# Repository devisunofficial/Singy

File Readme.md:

# Singy

This is an mp3 player I build because I wanted a mp3 player because having an MP3 player seems cool but not wanted to buy one.
It is inspired from iPod but it is not that good(I never had iPod). I just find Screen and Circular Controller a nice design.

### Features:

 - Minimilist. Just a display and Trackpad
 - 2.8 inch non touch display
 - Circular trackpad (but no haptics) {for me adding haptics is too much}
 - Have Wifi, Bluetooth and 3.5mm Headphone Jack (but I will only use 3.5mm Jack)
 - Inbuilt DAC and AMP (I hope it has good sound quality)

### CAD Model:
Everything fits together using Glue.

It has 3 separate printed pieces. The BackPanel, the shell , and Front Panel to cover electronics.

Made in Autodesk Fusion.
I didn't inserted 3D model for Display and Trackpad (Because I can't find)
So I will add this when it is completed!!

### PCB:
Here's my PCB! It was made in KiCad. 

Schematic : 
PCB Footprint : 

### Firmware Overview:
Currently Firmware is underdevelopment so there is some time to finished product.
This MP3 player uses CPP for firmware.
Features after completion:
 - Three ways to add new songs
    1. Directly in SD-Card
    2. Through USB Port
    3. Over Wi-fi.
 - The most important feature is it is offline but the Library is always updated
 - In final version, you need to save some of your favourite songs, and at your preferred date and time library will be updated.(Might need a server or device that has wifi and can run continously for this) 

 I might add more in the future! That's the only plan I have now

### BOM Table:
|S. No.|Name|Use|Quantity|
|------|----|---|-----------|
|1|PCB|Main Circuit|1|
|2|ESP32-S3 Wroom 1|Microcontroller|1|
|3|2.8inch Display|Display|1|
|4|Cirque TrackPad|Controlling and Navigation|1|
|5|Battery|Power Source |1|

### Assembly Instructions:
1. Flash PCB with Firmware, connect everything and check if everything is working or not
2. If Everything works, stick battery and PCB to their Respective places.
3. Also Stick Display and TrackPad Carefully to their places
4. Sltick all bodies together and Voila you have an MP3 player

### Extra Stuff:
 Not anything for now but I will surely have when the build is complete.

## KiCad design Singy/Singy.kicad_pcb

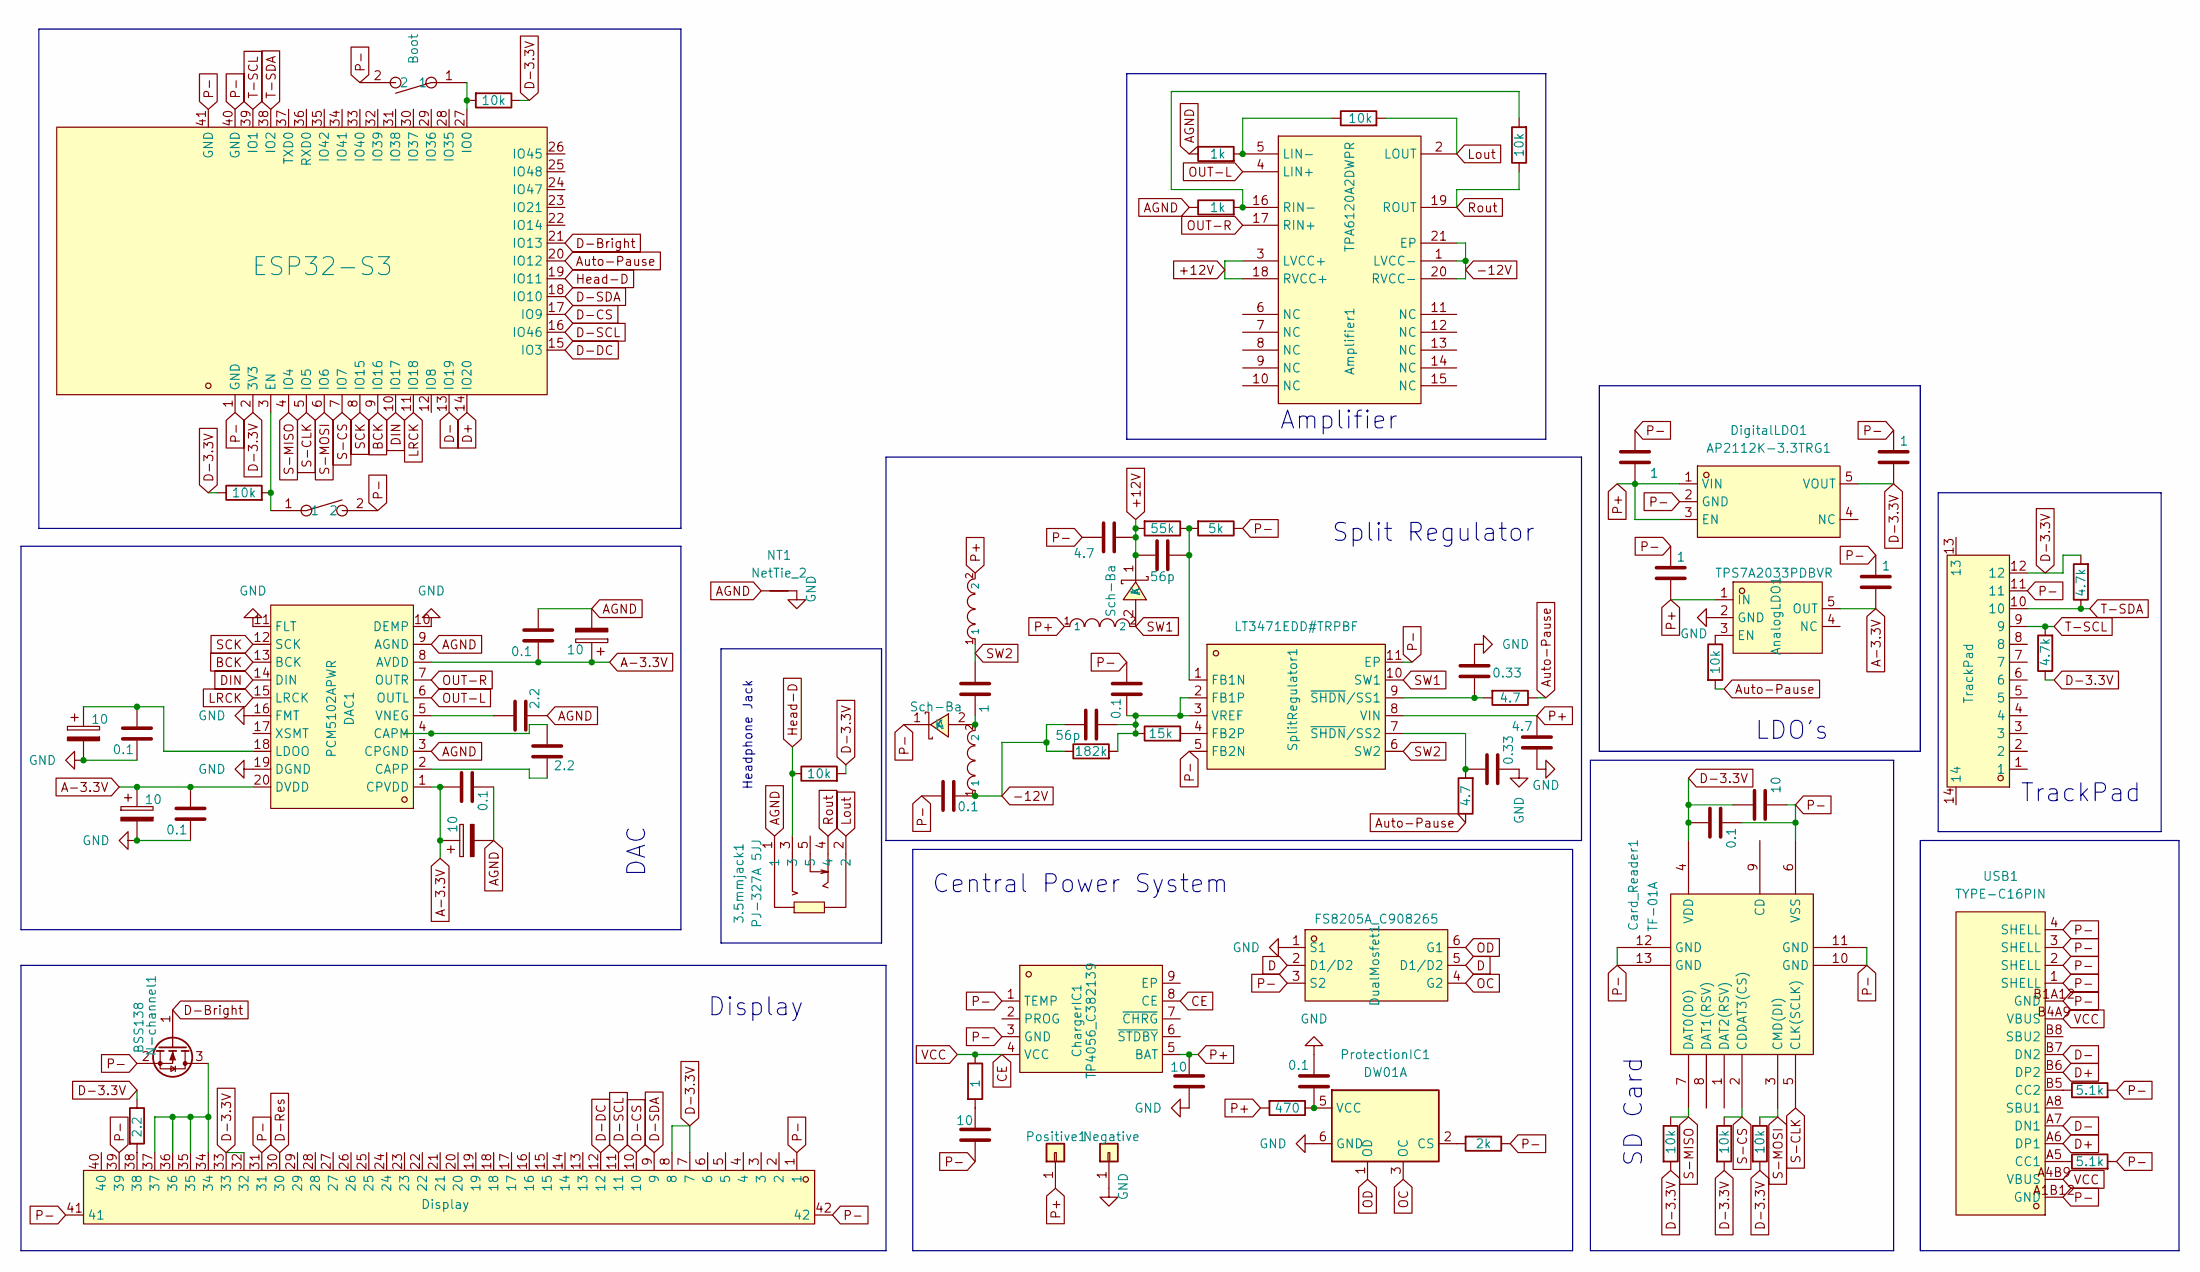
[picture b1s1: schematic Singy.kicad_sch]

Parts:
3.5mmjack1: PJ-327A 5JJ; AUDIO-SMD_PJ-327A5JJ; MPN PJ-327A 5JJ; LCSC Part C668605
Amplifier1: TPA6120A2DWPR; HSOP-20_L12.9-W7.5-P1.27-BL-EP; MPN TPA6120A2DWPR; LCSC Part C70439
AnalogLDO1: TPS7A2033PDBVR; SOT-23-5_L2.9-W1.6-P0.95-LS2.8-BR; MPN TPS7A2033PDBVR; LCSC Part C2862740
C1, C6: 2.2; C_0603_1608Metric
C2, C5, C8, C9, C20, C21, C24, C26: 0.1; C_0603_1608Metric
C3, C4, C7, C10, C18, C19, C27: 10; C_0603_1608Metric
C11, C12, C13, C14, C23: 1; C_0603_1608Metric
C15, C17: 0.33; C_0603_1608Metric
C16, C28: 4.7; C_0603_1608Metric
C22, C25: 56p; C_0603_1608Metric
Card_Reader1: TF-01A; TF-SMD_TF-01A; MPN TF-01A; LCSC Part C91145
ChargerIC1: TP4056_C382139; ESOP-8_L4.9-W3.9-P1.27-LS6.0-BL-EP; MPN TP4056; LCSC Part C382139
D1, D2: Sch-Ba; SMA_L4.4-W2.6-LS5.0-RD; MPN B230A-13-F; LCSC Part C12889
DAC1: PCM5102APWR; TSSOP-20_L6.5-W4.4-P0.65-LS6.4-BL; MPN PCM5102APWR; LCSC Part C107671
DigitalLDO1: AP2112K-3.3TRG1; SOT-25-5_L2.9-W1.6-P0.95-LS2.8-BL; MPN AP2112K-3.3TRG1; LCSC Part C51118
DualMosfet1: FS8205A_C908265; SOT-23-6_L2.9-W1.6-P0.95-LS2.8-BR; MPN FS8205A; LCSC Part C908265
FPC1: Display; FFC-SMD_541324062; MPN 541324062; LCSC Part C505102
J2: Negative; SolderWirePad_1x01_SMD_1x2mm
L1, L2: 10uH ±20%; C9389_IND-SMD_2P-L5_0-W5_0; LCSC C9389
L4: 10uH ±20%; C9164_IND-SMD_L5_8-W5_2; LCSC C9164
N-channel1: BSS138; SOT-23
NT1: NetTie_2; NetTie-2_SMD_Pad2.0mm
Positive1: Conn_01x01; SolderWirePad_1x01_SMD_1x2mm
ProtectionIC1: DW01A; SOT-23-6
R1, R2: 4.7; R_0805_2012Metric
R3: 1; R_0805_2012Metric
R4: 2k; R_0805_2012Metric
R5: 470; R_0805_2012Metric
R6: 15k; R_0805_2012Metric
R7: 182k; R_0805_2012Metric
R8: 55k; R_1206_3216Metric
R9: 5k; R_0805_2012Metric
R10, R11, R12, R14, R18, R19, R20, R23, R24: 10k; R_0805_2012Metric
R13, R25: 5.1k; R_0805_2012Metric
R15, R16: 4.7k; R_0805_2012Metric
R17: 2.2; R_0805_2012Metric
R21, R22: 1k; R_0805_2012Metric
SW2: Boot; SW-SMD_L6.0-W6.0-LS6.6; MPN SPEH110100; LCSC Part C97448
SW3: Reset; SW-SMD_L6.0-W6.0-LS6.6; MPN SPEH110100; LCSC Part C97448
SplitRegulator1: LT3471EDD#TRPBF; DFN-10_L3.0-W3.0-P0.50-BL-EP; MPN LT3471EDD#TRPBF; LCSC Part C514422
U1: ESP32-S3; WIRELM-SMD_ESP32-S3-WROOM-1; MPN ESP32-S3-WROOM-1-N16R8; LCSC Part C2913202
U2: TrackPad; FPC-SMD_12P-P0.50_HC-FPC-0.5-12P-FH20; MPN HC-FPC-0.5-12P-FH20; LCSC Part C19273928
USB1: TYPE-C16PIN; USB-C-SMD_TYPE-C16PIN; MPN TYPE-C16PIN; LCSC Part C393939

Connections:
+12V: Amplifier1.3 (LVCC+), Amplifier1.18 (RVCC+), C25.2, C28.1, D2.1 (K), R8.2
-12V: Amplifier1.1 (LVCC-), Amplifier1.20 (RVCC-), Amplifier1.21 (EP), C22.1, C24.2, L2.1, R7.1
A-3.3V: AnalogLDO1.5 (OUT), C2.1, C3.1, C4.1, C5.1, C7.1, C8.1, C14.2, DAC1.1 (CPVDD), DAC1.8 (AVDD), DAC1.20 (DVDD)
AGND: 3.5mmjack1.1, C2.2, C3.2, C4.2, C5.2, C6.1, DAC1.3 (CPGND), DAC1.9 (AGND), NT1.1, R21.1, R22.1
Auto-Pause: R1.1, R2.1, R14.2, U1.20 (IO12)
BCK: DAC1.13 (BCK), U1.9 (IO16)
CE: ChargerIC1.4 (VCC), ChargerIC1.8 (CE), R3.1, USB1.A4B9 (VBUS), USB1.B4A9 (VBUS)
D: DualMosfet1.2 (D1/D2), DualMosfet1.5 (D1/D2)
D+: U1.14 (IO20), USB1.A6 (DP1), USB1.B6 (DP2)
D-: U1.13 (IO19), USB1.A7 (DN1), USB1.B7 (DN2)
D-3.3V: C11.2, C26.1, C27.1, Card_Reader1.4 (VDD), DigitalLDO1.5 (VOUT), FPC1.7, FPC1.8, FPC1.32, FPC1.33, R10.2, R15.1, R16.2, R17.1, R18.2, R19.2, R20.2, R23.1, R24.1, U1.2 (3V3), U2.12
D-Bright: N-channel1.1 (G), U1.21 (IO13)
D-CS: FPC1.10, U1.17 (IO9)
D-DC: FPC1.12, U1.15 (IO3)
D-Res: FPC1.30
D-SCL: FPC1.11, U1.16 (IO46)
D-SDA: FPC1.9, U1.18 (IO10)
DIN: DAC1.14 (DIN), U1.10 (IO17)
GND: AnalogLDO1.2 (GND), C7.2, C8.2, C9.2, C10.2, C15.2, C16.1, C17.2, C19.2, C20.1, DAC1.10 (DEMP), DAC1.11 (FLT), DAC1.16 (FMT), DAC1.19 (DGND), DualMosfet1.1 (S1), J2.1 (Pin_1_1), NT1.2, ProtectionIC1.6 (GND)
Head-D: 3.5mmjack1.3, R10.1, U1.19 (IO11)
LRCK: DAC1.15 (LRCK), U1.11 (IO18)
Lout: 3.5mmjack1.2, Amplifier1.2 (LOUT), R12.2
unnamed: Amplifier1.5 (LIN-), R12.1, R21.2
unnamed: Amplifier1.16 (RIN-), R11.2, R22.2
unnamed: AnalogLDO1.3 (EN), R14.1
unnamed: C18.1, R3.2
unnamed: C23.2, D1.2 (A), L2.2
unnamed: C1.2, DAC1.4 (CAPM)
unnamed: C1.1, DAC1.2 (CAPP)
unnamed: C9.1, C10.1, DAC1.18 (LDOO)
unnamed: C6.2, DAC1.5 (VNEG)
unnamed: FPC1.38, R17.2
unnamed: FPC1.34, FPC1.35, FPC1.36, FPC1.37, N-channel1.3 (D)
unnamed: ProtectionIC1.2 (CS), R4.2
unnamed: C20.2, ProtectionIC1.5 (VCC), R5.1
unnamed: C25.1, R8.1, R9.2, SplitRegulator1.1 (FB1N)
unnamed: C21.2, C22.2, R6.1, R7.2, SplitRegulator1.2 (FB1P), SplitRegulator1.3 (VREF)
unnamed: R6.2, SplitRegulator1.4 (FB2P)
unnamed: C15.1, R1.2, SplitRegulator1.9 (~SHDN/SS1)
unnamed: C17.1, R2.2, SplitRegulator1.7 (~SHDN/SS2)
unnamed: R24.2, SW3.1, U1.3 (EN)
unnamed: R23.2, SW2.1, U1.27 (IO0)
unnamed: R25.1, USB1.A5 (CC1)
unnamed: R13.1, USB1.B5 (CC2)
OC: DualMosfet1.4 (G2), ProtectionIC1.3 (OC)
OD: DualMosfet1.6 (G1), ProtectionIC1.1 (OD)
OUT-L: Amplifier1.4 (LIN+), DAC1.6 (OUTL)
OUT-R: Amplifier1.17 (RIN+), DAC1.7 (OUTR)
P+: AnalogLDO1.1 (IN), C12.2, C13.2, C16.2, C19.1, ChargerIC1.5 (BAT), DigitalLDO1.1 (VIN), DigitalLDO1.3 (EN), L1.2, L4.1, Positive1.1 (Pin_1_1), R5.2, SplitRegulator1.8 (VIN)
P-: C11.1, C12.1, C13.1, C14.1, C18.2, C21.1, C24.1, C26.2, C27.2, C28.2, Card_Reader1.6 (VSS), Card_Reader1.10 (GND), Card_Reader1.11 (GND), Card_Reader1.12 (GND), Card_Reader1.13 (GND), ChargerIC1.1 (TEMP), ChargerIC1.3 (GND), D1.1 (K), DigitalLDO1.2 (GND), DualMosfet1.3 (S2), FPC1.1, FPC1.31, FPC1.39, FPC1.41, FPC1.42, N-channel1.2 (S), R4.1, R9.1, R13.2, R25.2, SW2.2, SW3.2, SplitRegulator1.5 (FB2N), SplitRegulator1.11 (EP), U1.1 (GND), U1.40 (GND), U1.41 (GND), U2.11, USB1.1 (SHELL), USB1.2 (SHELL), USB1.3 (SHELL), USB1.4 (SHELL), USB1.A1B12 (GND), USB1.B1A12 (GND)
Rout: 3.5mmjack1.4, Amplifier1.19 (ROUT), R11.1
S-CLK: Card_Reader1.5 (CLK(SCLK)), U1.5 (IO5)
S-CS: Card_Reader1.2 (CDDAT3(CS)), R18.1, U1.7 (IO7)
S-MISO: Card_Reader1.7 (DAT0(D0)), R20.1, U1.4 (IO4)
S-MOSI: Card_Reader1.3 (CMD(DI)), R19.1, U1.6 (IO6)
SCK: DAC1.12 (SCK), U1.8 (IO15)
SW1: D2.2 (A), L4.2, SplitRegulator1.10 (SW1)
SW2: C23.1, L1.1, SplitRegulator1.6 (SW2)
T-SCL: R15.2, U1.39 (IO1), U2.9
T-SDA: R16.1, U1.38 (IO2), U2.10

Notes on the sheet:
LDO's
Amplifier
Central Power System
TrackPad
Display
Split Regulator
SD Card
Headphone Jack
DAC

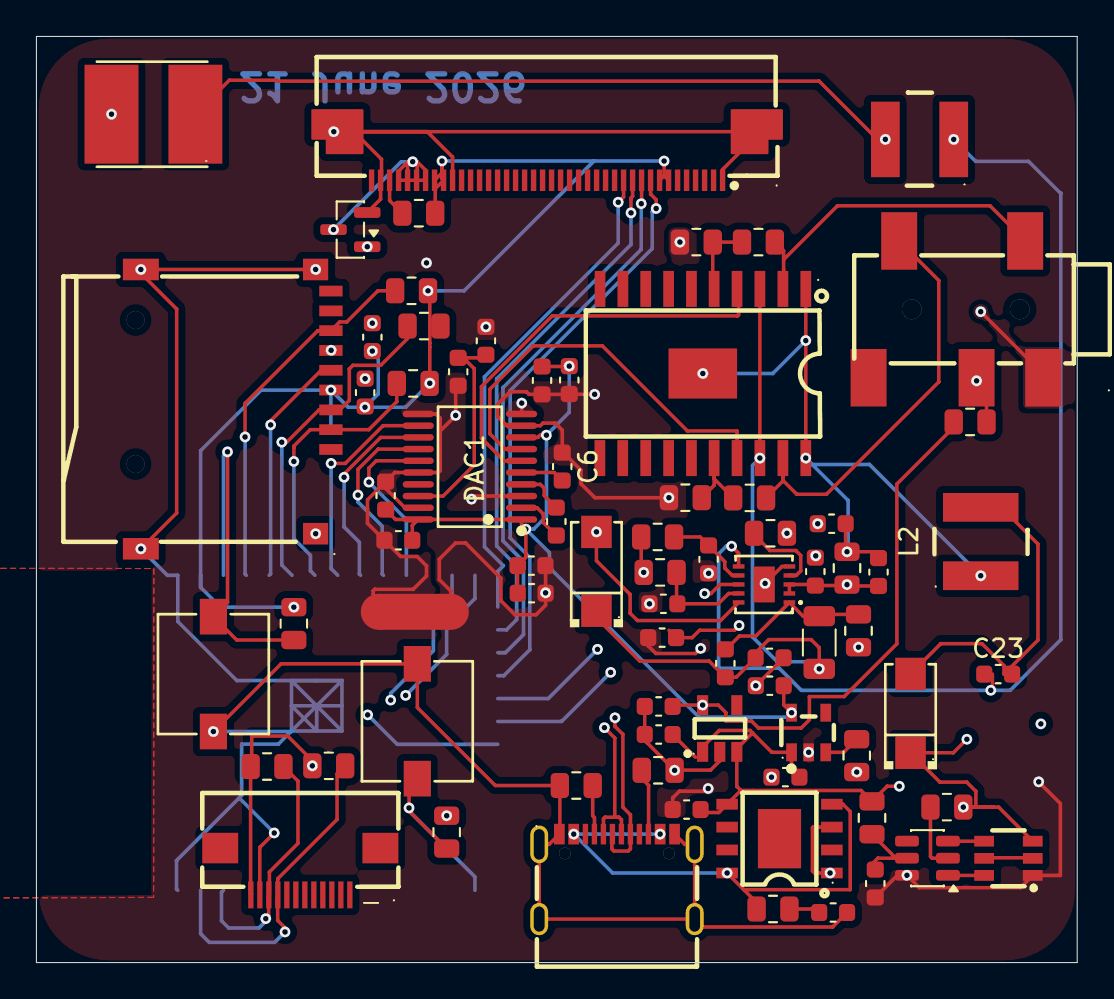
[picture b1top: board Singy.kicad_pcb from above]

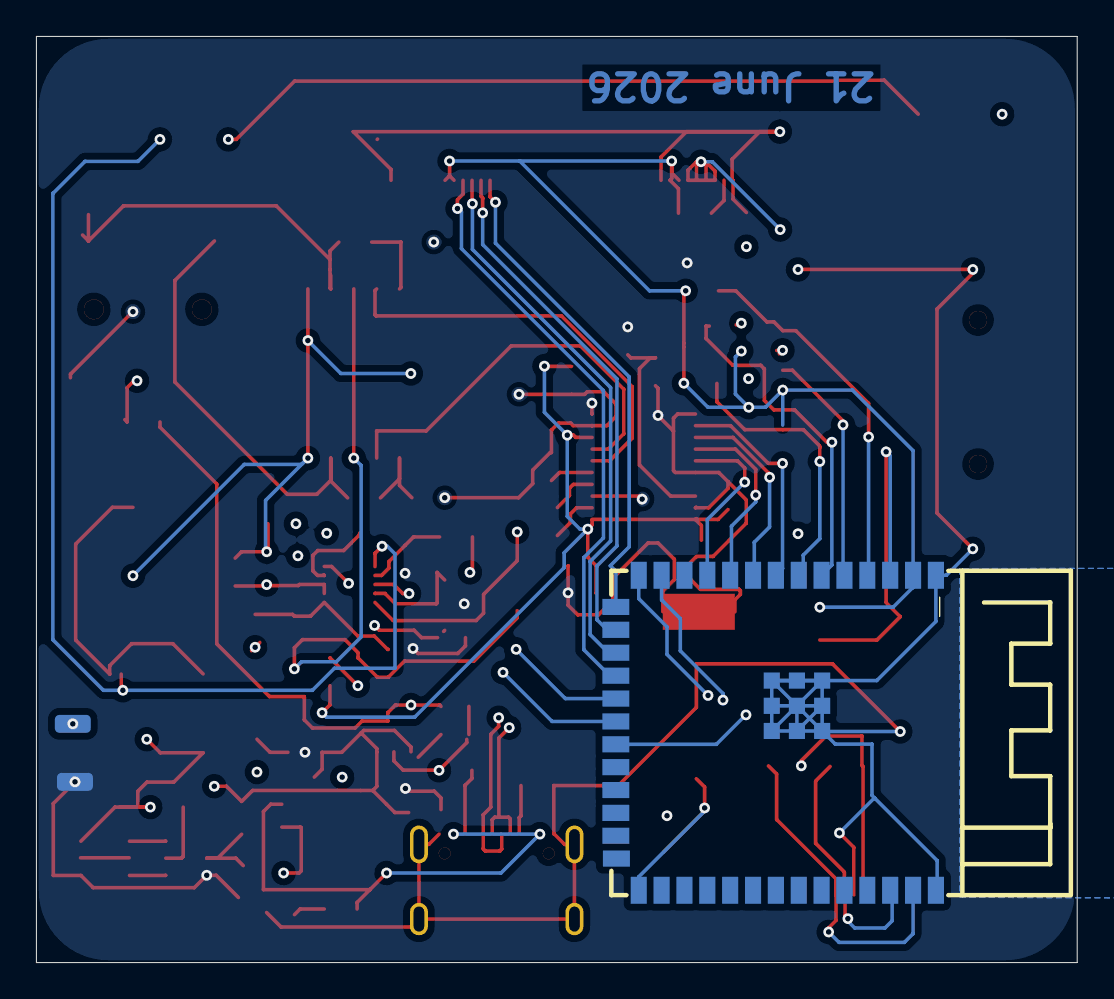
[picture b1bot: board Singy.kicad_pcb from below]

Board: 4 copper layers, 57.8 x 51.5 mm, 78 parts (3 on the bottom side), 59 nets.

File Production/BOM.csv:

Comment,Designator,Footprint
PJ-327A 5JJ,3.5mmjack1,AUDIO-SMD_PJ-327A5JJ
TPA6120A2DWPR,Amplifier1,HSOP-20_L12.9-W7.5-P1.27-BL-EP
TPS7A2033PDBVR,AnalogLDO1,SOT-23-5_L2.9-W1.6-P0.95-LS2.8-BR
2.2,"C1, C6",C_0603_1608Metric
0.1,"C2, C5, C8, C9, C20, C21, C24, C26",C_0603_1608Metric
10,"C3, C4, C7, C10, C18, C19, C27",C_0603_1608Metric
1,"C11, C12, C13, C14, C23",C_0603_1608Metric
0.33,"C15, C17",C_0603_1608Metric
4.7,"C16, C28",C_0603_1608Metric
56p,"C22, C25",C_0603_1608Metric
TF-01A,Card_Reader1,TF-SMD_TF-01A
TP4056_C382139,ChargerIC1,ESOP-8_L4.9-W3.9-P1.27-LS6.0-BL-EP
Sch-Ba,"D1, D2",SMA_L4.4-W2.6-LS5.0-RD
PCM5102APWR,DAC1,TSSOP-20_L6.5-W4.4-P0.65-LS6.4-BL
AP2112K-3.3TRG1,DigitalLDO1,SOT-25-5_L2.9-W1.6-P0.95-LS2.8-BL
FS8205A_C908265,DualMosfet1,SOT-23-6_L2.9-W1.6-P0.95-LS2.8-BR
Display,FPC1,FFC-SMD_541324062
10uH ±20%,"L1, L2",C9389_IND-SMD_2P-L5_0-W5_0
10uH ±20%,L4,C9164_IND-SMD_L5_8-W5_2
BSS138,N-channel1,SOT-23
DW01A,ProtectionIC1,SOT-23-6
4.7,"R1, R2",R_0805_2012Metric
1,R3,R_0805_2012Metric
2k,R4,R_0805_2012Metric
470,R5,R_0805_2012Metric
15k,R6,R_0805_2012Metric
182k,R7,R_0805_2012Metric
55k,R8,R_1206_3216Metric
5k,R9,R_0805_2012Metric
10k,"R10, R11, R12, R14, R18, R19, R20, R23, R24",R_0805_2012Metric
5.1k,"R13, R25",R_0805_2012Metric
4.7k,"R15, R16",R_0805_2012Metric
2.2,R17,R_0805_2012Metric
1k,"R21, R22",R_0805_2012Metric
LT3471EDD#TRPBF,SplitRegulator1,DFN-10_L3.0-W3.0-P0.50-BL-EP
Boot,SW2,SW-SMD_L6.0-W6.0-LS6.6
Reset,SW3,SW-SMD_L6.0-W6.0-LS6.6
TrackPad,U2,FPC-SMD_12P-P0.50_HC-FPC-0.5-12P-FH20
TYPE-C16PIN,USB1,USB-C-SMD_TYPE-C16PIN
